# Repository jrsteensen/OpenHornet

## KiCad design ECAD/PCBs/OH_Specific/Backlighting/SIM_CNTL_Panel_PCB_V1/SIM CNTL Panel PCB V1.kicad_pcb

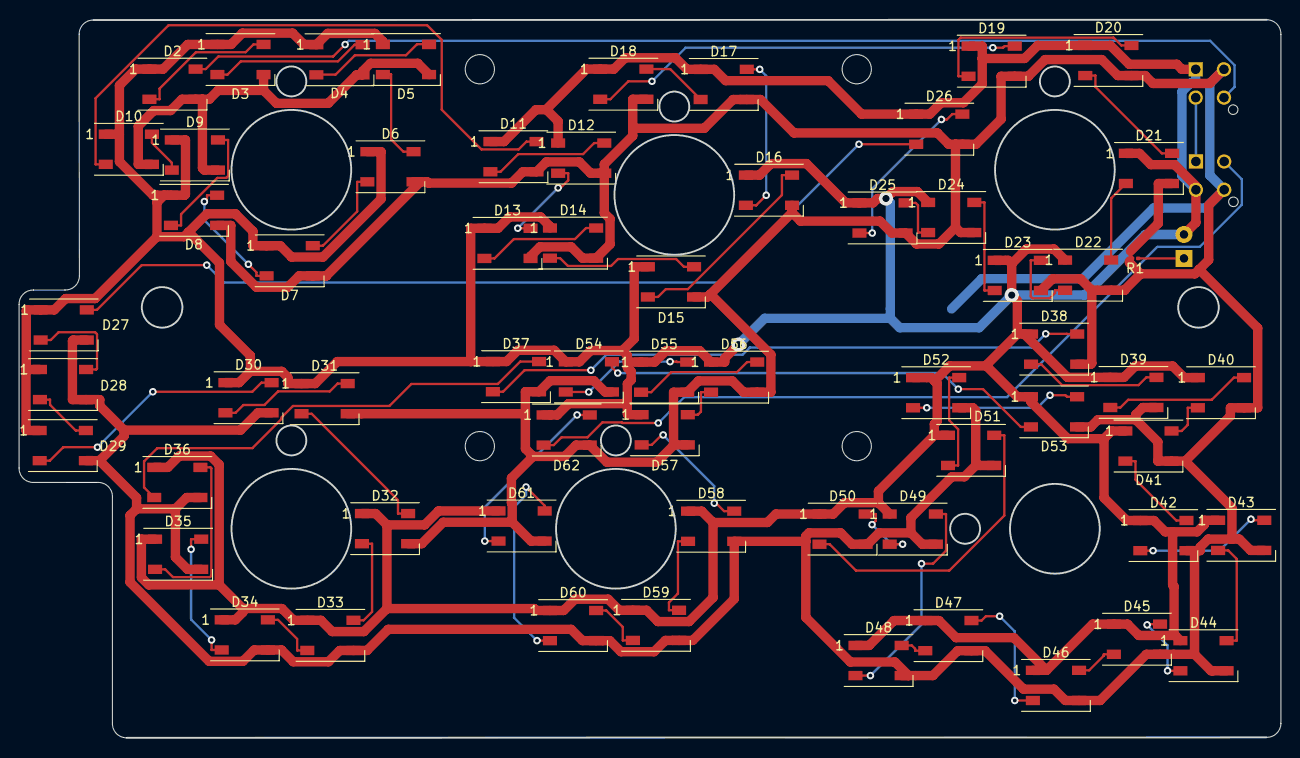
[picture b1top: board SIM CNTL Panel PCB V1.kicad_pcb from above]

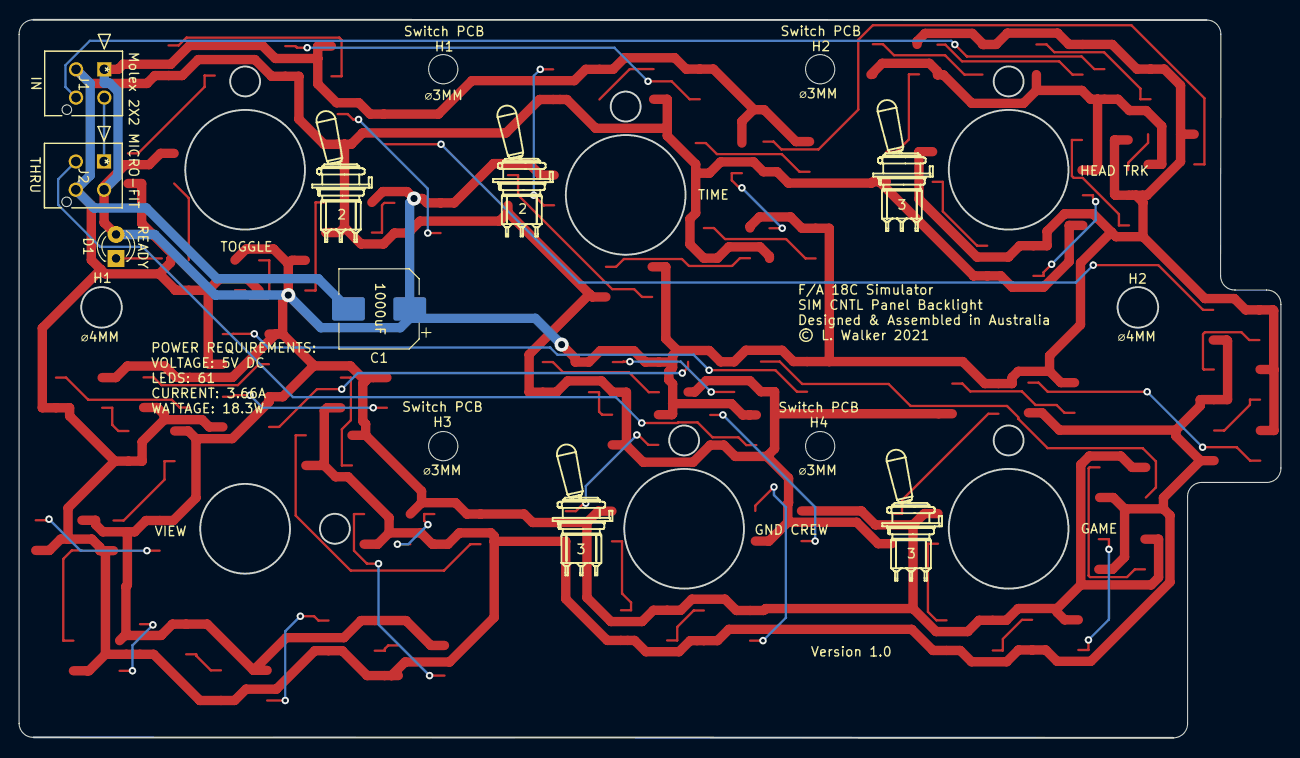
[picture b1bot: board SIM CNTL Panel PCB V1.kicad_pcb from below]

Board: 2 copper layers, 133.9 x 76.2 mm, 71 parts (4 on the bottom side), 66 nets.

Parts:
C1: C_Polarized; CP_Elec_8x10
D1: LED; LED_D3.0mm
D2, D3, D4, D5, D6, D7, D8, D9, D10, D11, D12, D13, D14, D15, D16, D17, D18, D19, D20, D21, D22, D23, D24, D25, D26, D27, D28, D29, D30, D31, D32, D33, D34, D35, D36, D37, D38, D39, D40, D41, D42, D43, D44, D45, D46, D47, D48, D49, D50, D51, D52, D53, D54, D55, D56, D57, D58, D59, D60, D61, D62: WS2812B; LED_WS2812B_PLCC4_5.0x5.0mm_P3.2mm
G1, G2, G3, G4, G5: LOGO; 100SpxToggle
J1, J2: Conn_01x04_Female; Molex_MicroFit_2X2
R1: R; R_0201_0603Metric

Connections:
/DATAIN: D2.4, J1.4
/DATALOOP: J1.2, J2.1
/DATAOUT: D62.2, J2.3
/LED+5V: C1.1, D1.2, D2.1, D3.1, D4.1, D5.1, D6.1, D7.1, D8.1, D9.1, D10.1, D11.1, D12.1, D13.1, D14.1, D15.1, D16.1, D17.1, D18.1, D19.1, D20.1, D21.1, D22.1, D23.1, D24.1, D25.1, D26.1, D27.1, D28.1, D29.1, D30.1, D31.1, D32.1, D33.1, D34.1, D35.1, D36.1, D37.1, D38.1, D39.1, D40.1, D41.1, D42.1, D43.1, D44.1, D45.1, D46.1, D47.1, D48.1, D49.1, D50.1, D51.1, D52.1, D53.1, D54.1, D55.1, D56.1, D57.1, D58.1, D59.1, D60.1, D61.1, D62.1, J1.1, J2.2
/LEDGND: C1.2, D2.3, D3.3, D4.3, D5.3, D6.3, D7.3, D8.3, D9.3, D10.3, D11.3, D12.3, D13.3, D14.3, D15.3, D16.3, D17.3, D18.3, D19.3, D20.3, D21.3, D22.3, D23.3, D24.3, D25.3, D26.3, D27.3, D28.3, D29.3, D30.3, D31.3, D32.3, D33.3, D34.3, D35.3, D36.3, D37.3, D38.3, D39.3, D40.3, D41.3, D42.3, D43.3, D44.3, D45.3, D46.3, D47.3, D48.3, D49.3, D50.3, D51.3, D52.3, D53.3, D54.3, D55.3, D56.3, D57.3, D58.3, D59.3, D60.3, D61.3, D62.3, J1.3, J2.4, R1.2
unnamed: D1.1, R1.1
unnamed: D2.2, D3.4
unnamed: D3.2, D4.4
unnamed: D4.2, D5.4
unnamed: D5.2, D6.4
unnamed: D6.2, D7.4
unnamed: D7.2, D8.4
unnamed: D8.2, D9.4
unnamed: D10.2, D11.4
unnamed: D9.2, D10.4
unnamed: D11.2, D12.4
unnamed: D12.2, D13.4
unnamed: D13.2, D14.4
unnamed: D14.2, D15.4
unnamed: D15.2, D16.4
unnamed: D16.2, D17.4
unnamed: D17.2, D18.4
unnamed: D18.2, D19.4
unnamed: D19.2, D20.4
unnamed: D20.2, D21.4
unnamed: D21.2, D22.4
unnamed: D22.2, D23.4
unnamed: D23.2, D24.4
unnamed: D24.2, D25.4
unnamed: D25.2, D26.4
unnamed: D26.2, D27.4
unnamed: D27.2, D28.4
unnamed: D28.2, D29.4
unnamed: D29.2, D30.4
unnamed: D30.2, D31.4
unnamed: D31.2, D32.4
unnamed: D32.2, D33.4
unnamed: D33.2, D34.4
unnamed: D34.2, D35.4
unnamed: D35.2, D36.4
unnamed: D36.2, D37.4
unnamed: D37.2, D38.4
unnamed: D38.2, D39.4
unnamed: D39.2, D40.4
unnamed: D40.2, D41.4
unnamed: D41.2, D42.4
unnamed: D42.2, D43.4
unnamed: D43.2, D44.4
unnamed: D44.2, D45.4
unnamed: D45.2, D46.4
unnamed: D46.2, D47.4
unnamed: D47.2, D48.4
unnamed: D48.2, D49.4
unnamed: D49.2, D50.4
unnamed: D50.2, D51.4
unnamed: D51.2, D52.4
unnamed: D52.2, D53.4
unnamed: D53.2, D54.4
unnamed: D54.2, D55.4
unnamed: D55.2, D56.4
unnamed: D56.2, D57.4
unnamed: D57.2, D58.4
unnamed: D58.2, D59.4
unnamed: D59.2, D60.4
unnamed: D60.2, D61.4
unnamed: D61.2, D62.4

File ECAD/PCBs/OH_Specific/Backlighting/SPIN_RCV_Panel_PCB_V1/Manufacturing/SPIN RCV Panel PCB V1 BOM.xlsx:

Comment | Designator | Footprint | LCSC Part #
LED | D52,D50,D48,D47,D46,D43,D42,D41,D38,D31,D28,D27,D26,D24,D23,D22,D21,D20,D19,D18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 | LED-4_5050 | C114586
LED | D53,D51,D49,D45,D44,D40,D39,D37,D36,D35,D34,D33,D32,D30,D29,D25 | LED-4_3535 | C114583
Resistor 470 ohm | R1 | 0603 | C23179

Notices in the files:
ECAD/PCBs/OH_Specific/Backlighting/SIM_CNTL_Panel_PCB_V1/SIM CNTL Panel PCB V1.kicad_pcb:
© L. Walker 2021
parts and their libraries:
Copyright 2016 Accelerated Designs. All rights reserved.
